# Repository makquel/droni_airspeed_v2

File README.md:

# droni_airspeed_v2
Proprietary hardware airspeed sensor for airship UAV

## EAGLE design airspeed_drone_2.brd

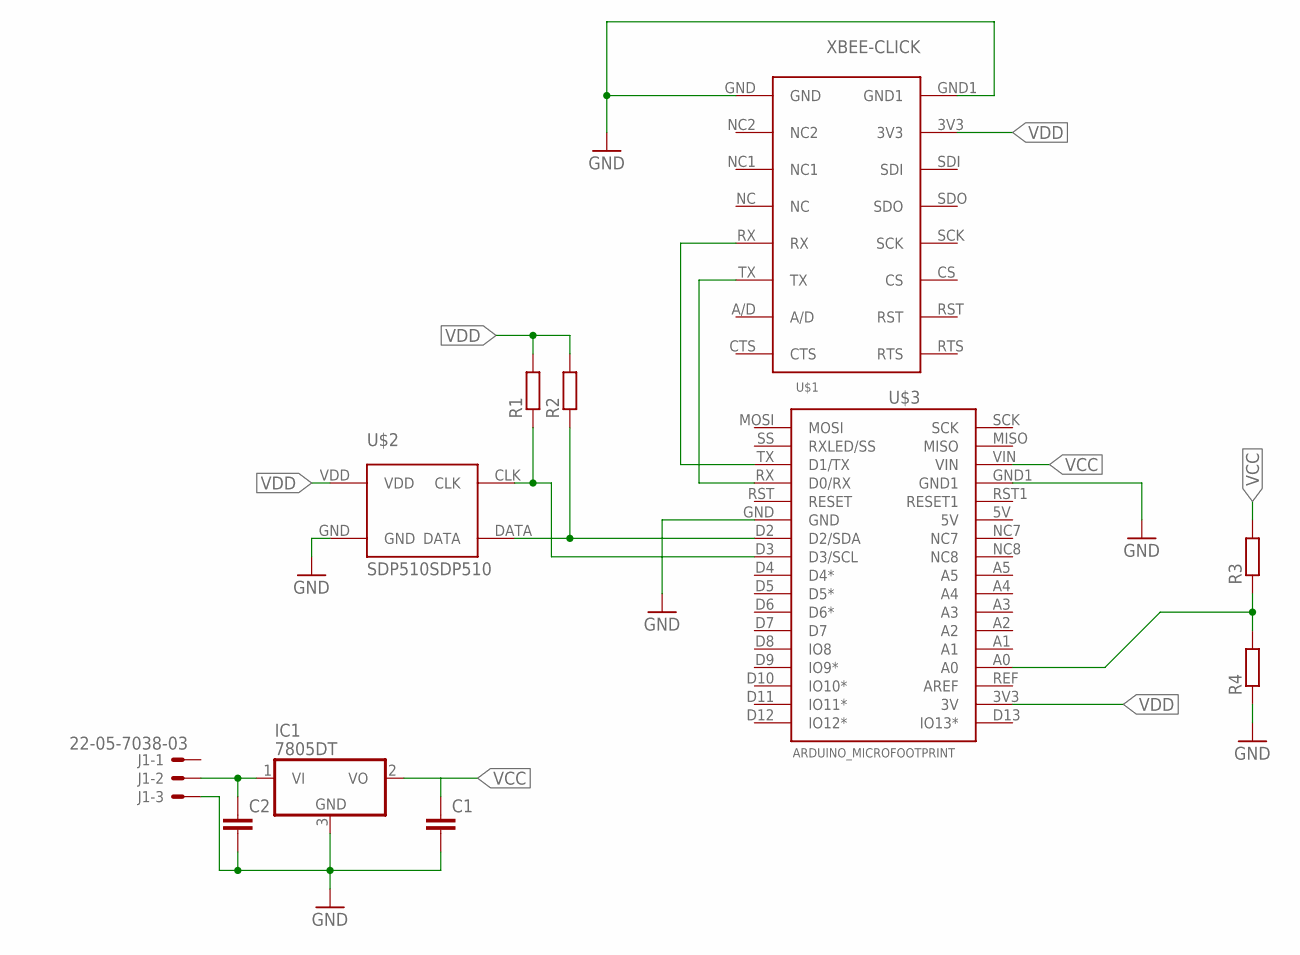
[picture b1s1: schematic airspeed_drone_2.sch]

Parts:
C1, C2: C-EUC0805K; C0805K
IC1: 7805DT; TO252
J1: 22-05-7038-03; 7395-03
R1, R2: R-EU_R0603; R0603
R3, R4: R-EU_R0805; R0805
U$1: ARDUINO_MICROFOOTPRINT; ARDUINO-MICRO
U$2: SDP510SDP510; SDP510
U$3: XBEE-CLICK; XBEE-CLK

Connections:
GND: C1.2, C2.2, IC1.3 (GND), J1.3, R4.1, U$1.GND, U$1.GND1, U$2.GND, U$3.GND, U$3.GND1
unnamed: C2.1, IC1.1 (VI), J1.2
unnamed: R1.1, U$1.D3 (D3/SCL), U$2.CLK
unnamed: R2.1, U$1.D2 (D2/SDA), U$2.DATA
unnamed: U$1.RX (D0/RX), U$3.TX
unnamed: U$1.TX (D1/TX), U$3.RX
unnamed: R3.1, R4.2, U$1.A0
VCC: C1.1, IC1.2 (VO), R3.2, U$1.VIN
VDD: R1.2, R2.2, U$1.3V3 (3V), U$2.VDD, U$3.3V3

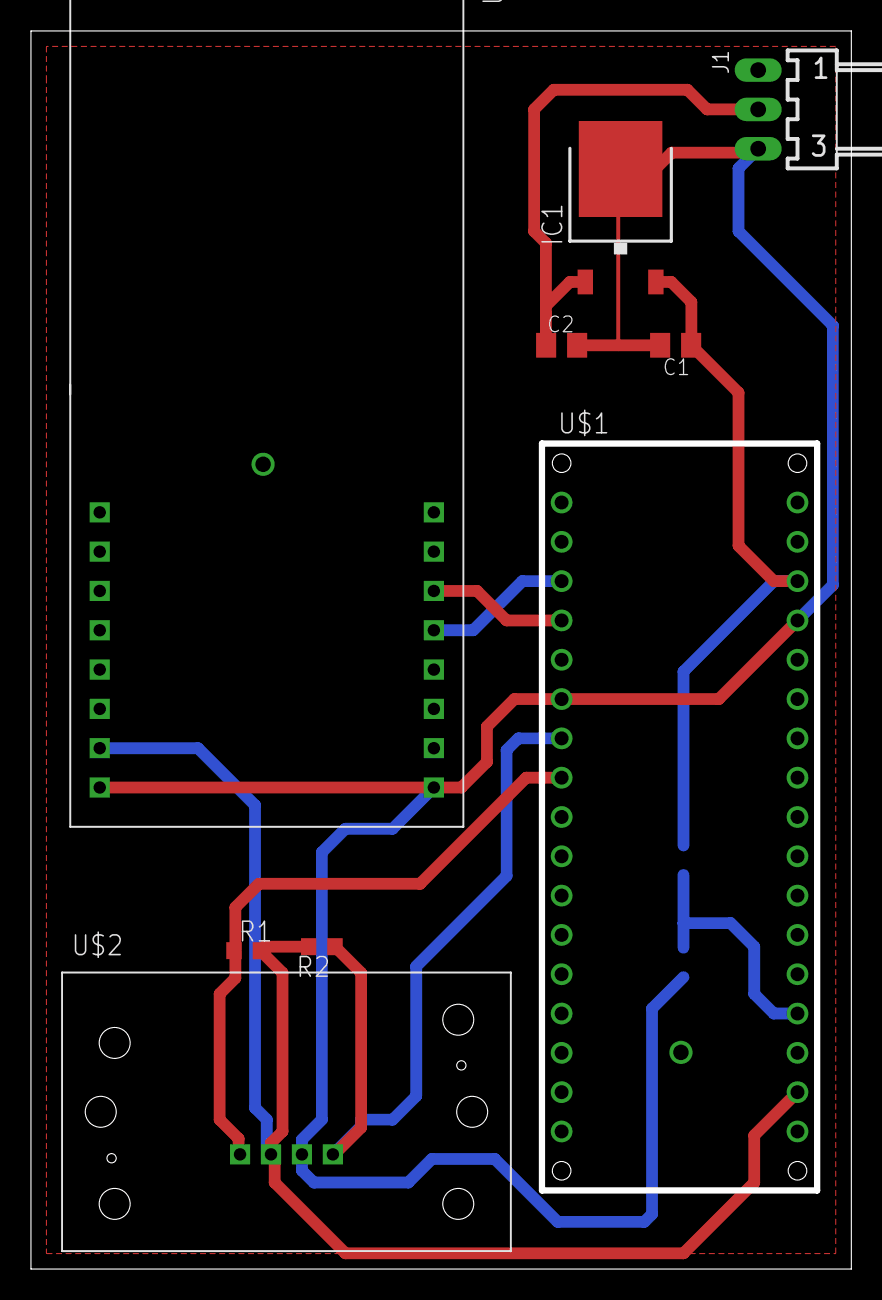
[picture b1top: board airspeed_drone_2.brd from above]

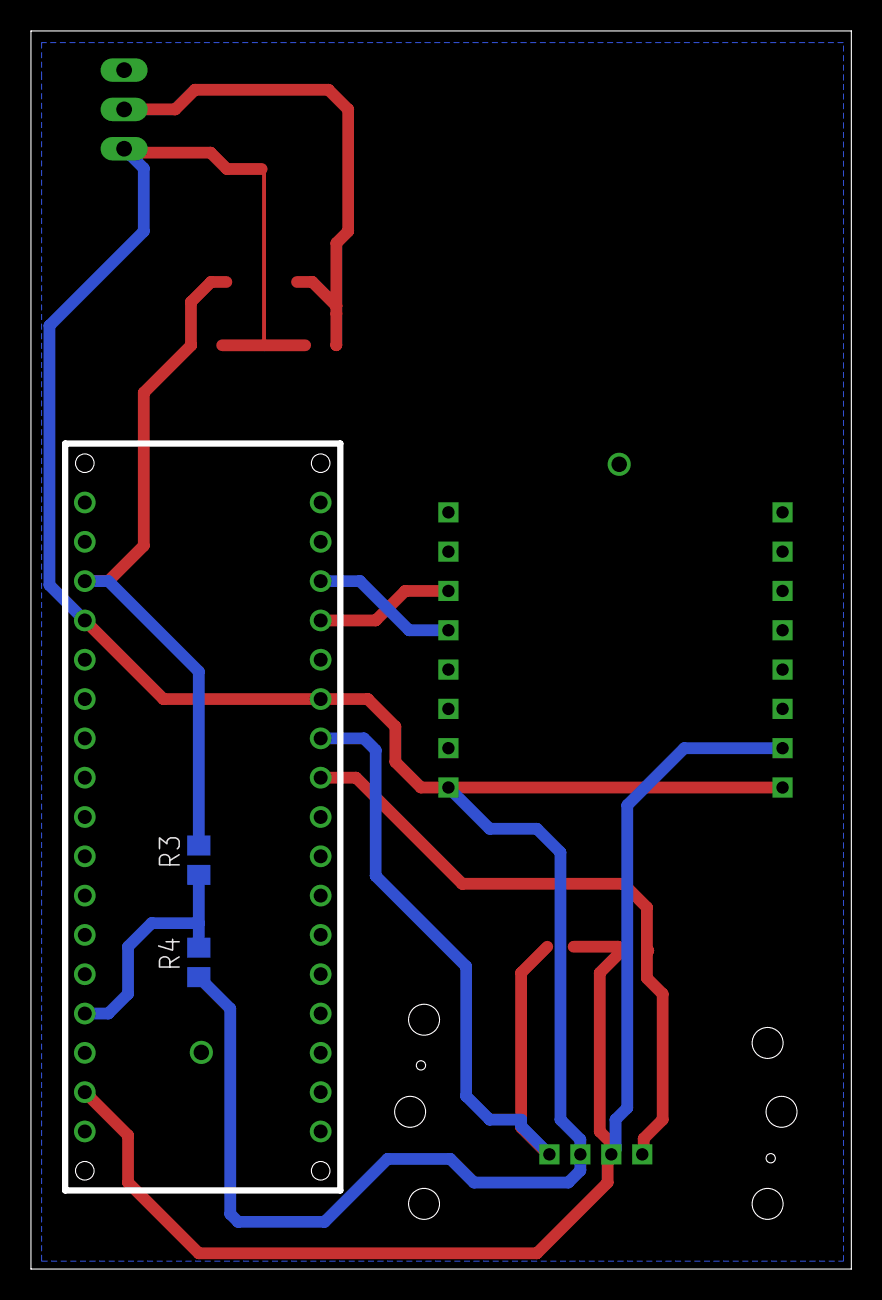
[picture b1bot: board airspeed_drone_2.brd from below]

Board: 2 copper layers, 53.0 x 80.0 mm, 11 parts (2 on the bottom side), 9 nets.

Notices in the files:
parts and their libraries:
sensirion: Copyright (C) 2011, Bob Starr
